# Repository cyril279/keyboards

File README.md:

# One42 | low-profile 42-key Wireless
choc-v2 & v1 switches, MX-spaced, integrated/onboard nrf52840 controller  

# rev41l2 / 41-1353 | low-profile Reviung41 variant
choc-v2 & v1 switches, MX-spaced  

# rev41lp / 41-1350 | low-profile Reviung41 variant
choc-v1 switches, choc-spaced, hotswap, single-color backlit

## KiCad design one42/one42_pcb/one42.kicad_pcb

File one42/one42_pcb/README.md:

[<< Link to Schematic (one42.pdf) >>](./one42.pdf)

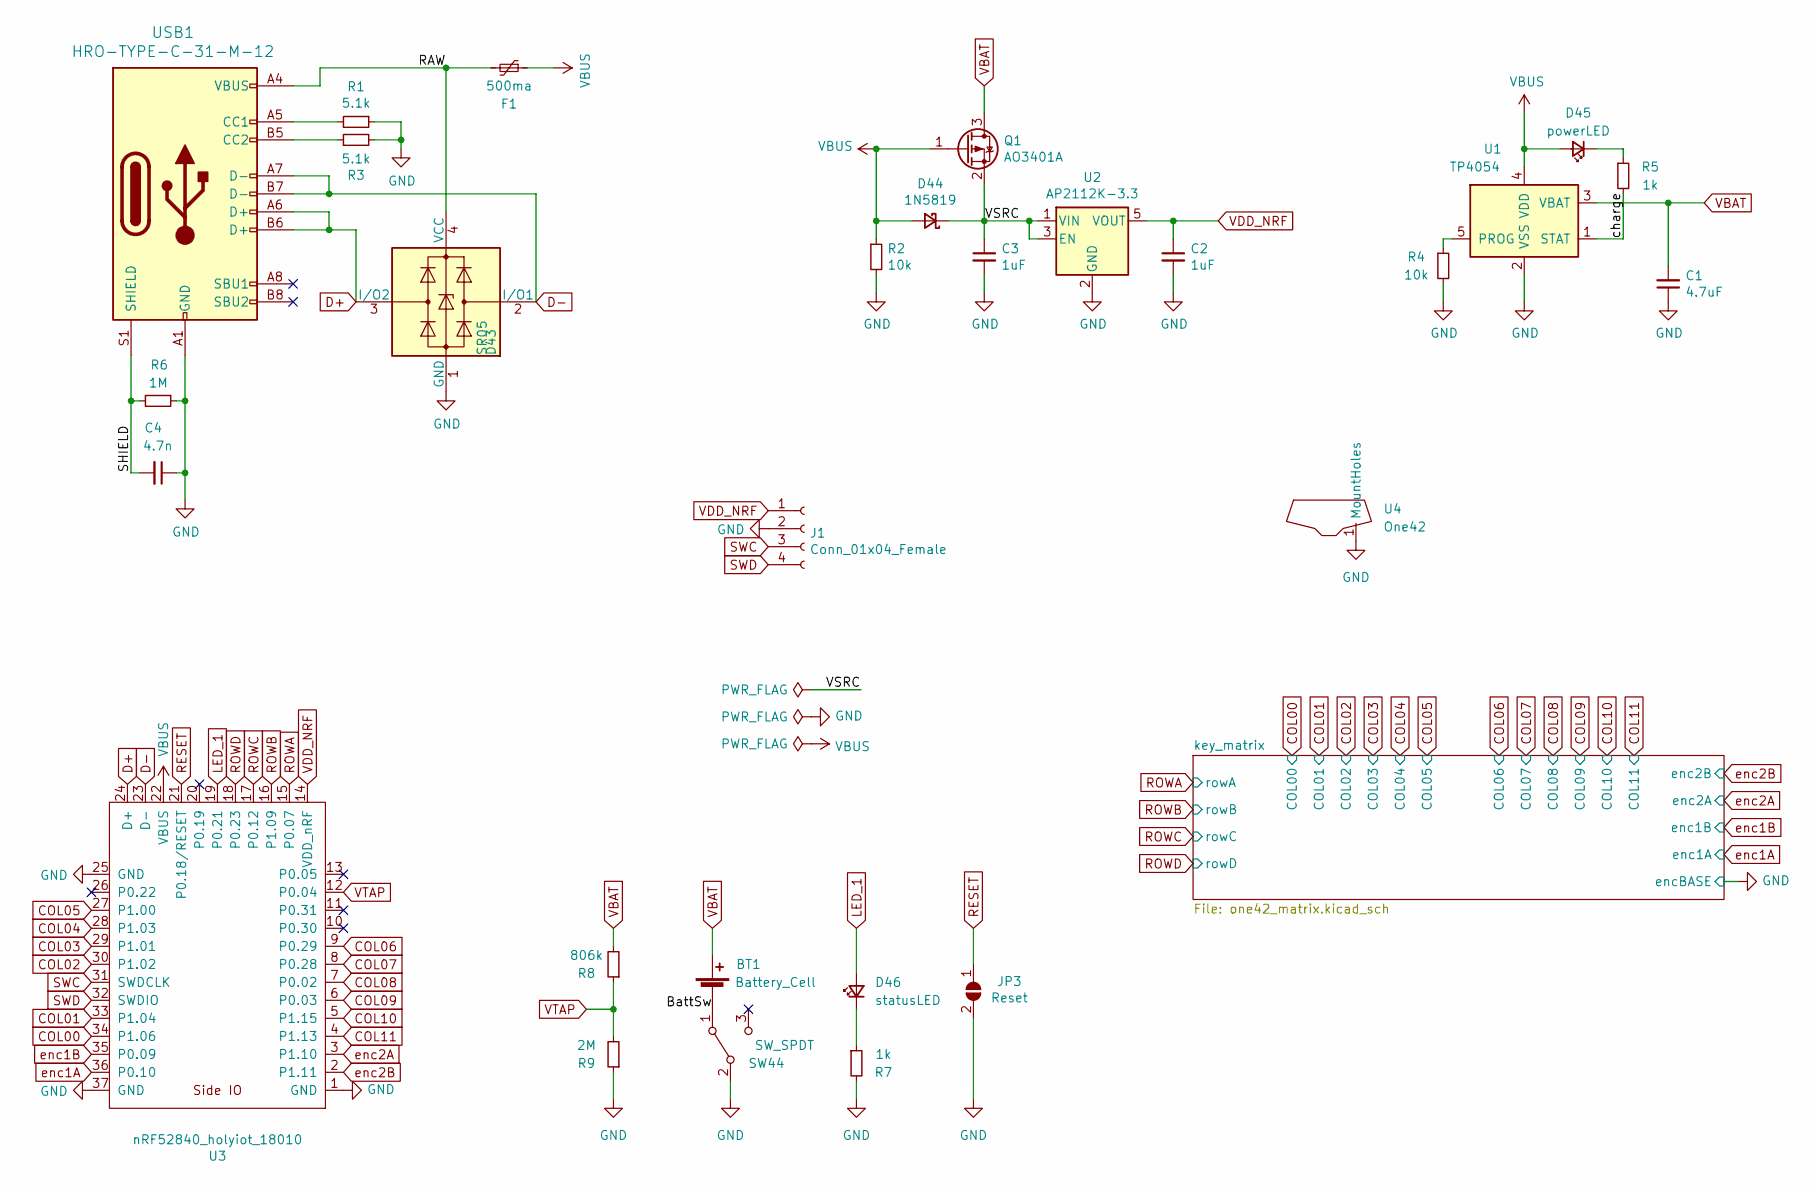
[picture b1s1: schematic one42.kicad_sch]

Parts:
BT1: Battery_Cell; cell_pads
C1: 4.7uF; C_0805_2012Metric; JLC 0805
C2, C3: 1uF; C_0805_2012Metric; JLC 0805
C4: 4.7n; C_1206_3216Metric
D43: SR05; SOT-143
D44: 1N5819; D_SOD-123
D45: powerLED; D_0805_2012Metric
D46: statusLED; D_0805_2012Metric
F1: 500ma; Fuse_1206_3216Metric
J1: Conn_01x04_Female; PinHeader_1x04_P2.54mm_Vertical
JP3: Reset; SolderJumper-2_P1.3mm_Open_RoundedPad1.0x1.5mm
Q1: AO3401A; SOT-23; JLC SOT-23-3L
R1, R3: 5.1k; R_0805_2012Metric; JLC 0805
R2, R4: 10k; R_0805_2012Metric; JLC 0805
R5, R7: 1k; R_0805_2012Metric; JLC 0805
R6: 1M; R_0805_2012Metric; JLC 0805
R8: 806k; R_0805_2012Metric
R9: 2M; R_0805_2012Metric; JLC 0805
SW44: SW_SPDT; switch_SSSS811101
U1: TP4054; SOT-23-5; JLC SOT-23-5
U2: AP2112K-3.3; SOT-23-5
U3: nRF52840_holyiot_18010; nRF52840_holyiot_18010_HS_simple
U4: One42; one42
USB1: HRO-TYPE-C-31-M-12; USB_C_Receptacle_HRO_TYPE-C-31-M-12_handsolder

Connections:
/BattSw: BT1.2 (-), SW44.1 (A)
/RAW: D43.4 (VCC), F1.2, USB1.A4 (VBUS), USB1.A9 (VBUS), USB1.B4 (VBUS), USB1.B9 (VBUS)
/SHIELD: C4.2, R6.2, USB1.S1 (SHIELD)
/VSRC: C3.1, D44.1 (K), Q1.2 (S), U2.1 (VIN), U2.3 (EN)
/charge: R5.2, U1.1 (STAT)
COL00: U3.34 (P1.06); also elsewhere on the board
COL01: U3.33 (P1.04); also elsewhere on the board
COL02: U3.30 (P1.02); also elsewhere on the board
COL03: U3.29 (P1.01); also elsewhere on the board
COL04: U3.28 (P1.03); also elsewhere on the board
COL05: U3.27 (P1.00); also elsewhere on the board
COL06: U3.9 (P0.29); also elsewhere on the board
COL07: U3.8 (P0.28); also elsewhere on the board
COL08: U3.7 (P0.02); also elsewhere on the board
COL09: U3.6 (P0.03); also elsewhere on the board
COL10: U3.5 (P1.15); also elsewhere on the board
COL11: U3.4 (P1.13); also elsewhere on the board
D+: D43.3 (I/O2), U3.24 (D+), USB1.A6 (D+), USB1.B6 (D+)
D-: D43.2 (I/O1), U3.23 (D-), USB1.A7 (D-), USB1.B7 (D-)
GND: C1.1, C2.2, C3.2, C4.1, D43.1 (GND), J1.2, JP3.2 (B), R1.1, R2.2, R3.2, R4.2, R6.1, R7.2, R9.1, SW44.2 (B), U1.2 (VSS), U2.2 (GND), U3.1 (GND), U3.25 (GND), U3.37 (GND), U4.1 (MountHoles), USB1.A1 (GND), USB1.A12 (GND), USB1.B1 (GND), USB1.B12 (GND); also elsewhere on the board
LED_1: D46.2 (A), U3.19 (P0.21)
unnamed: D45.1 (K), R5.1
unnamed: D46.1 (K), R7.1
unnamed: R1.2, USB1.A5 (CC1)
unnamed: R3.1, USB1.B5 (CC2)
unnamed: R4.1, U1.5 (PROG)
RESET: JP3.1 (A), U3.21 (P0.18/RESET)
ROWA: U3.15 (P0.07); also elsewhere on the board
ROWB: U3.16 (P1.09); also elsewhere on the board
ROWC: U3.17 (P0.12); also elsewhere on the board
ROWD: U3.18 (P0.23); also elsewhere on the board
SWC: J1.3, U3.31 (SWDCLK)
SWD: J1.4, U3.32 (SWDIO)
VBAT: BT1.1 (+), C1.2, Q1.3 (D), R8.2, U1.3 (VBAT)
VBUS: D44.2 (A), D45.2 (A), F1.1, Q1.1 (G), R2.1, U1.4 (VDD), U3.22 (VBUS)
VDD_NRF: C2.1, J1.1, U2.5 (VOUT), U3.14 (VDD_nRF)
VTAP: R8.1, R9.2, U3.12 (P0.04)
enc1A: U3.36 (P0.10); also elsewhere on the board
enc1B: U3.35 (P0.09); also elsewhere on the board
enc2A: U3.3 (P1.10); also elsewhere on the board
enc2B: U3.2 (P1.11); also elsewhere on the board

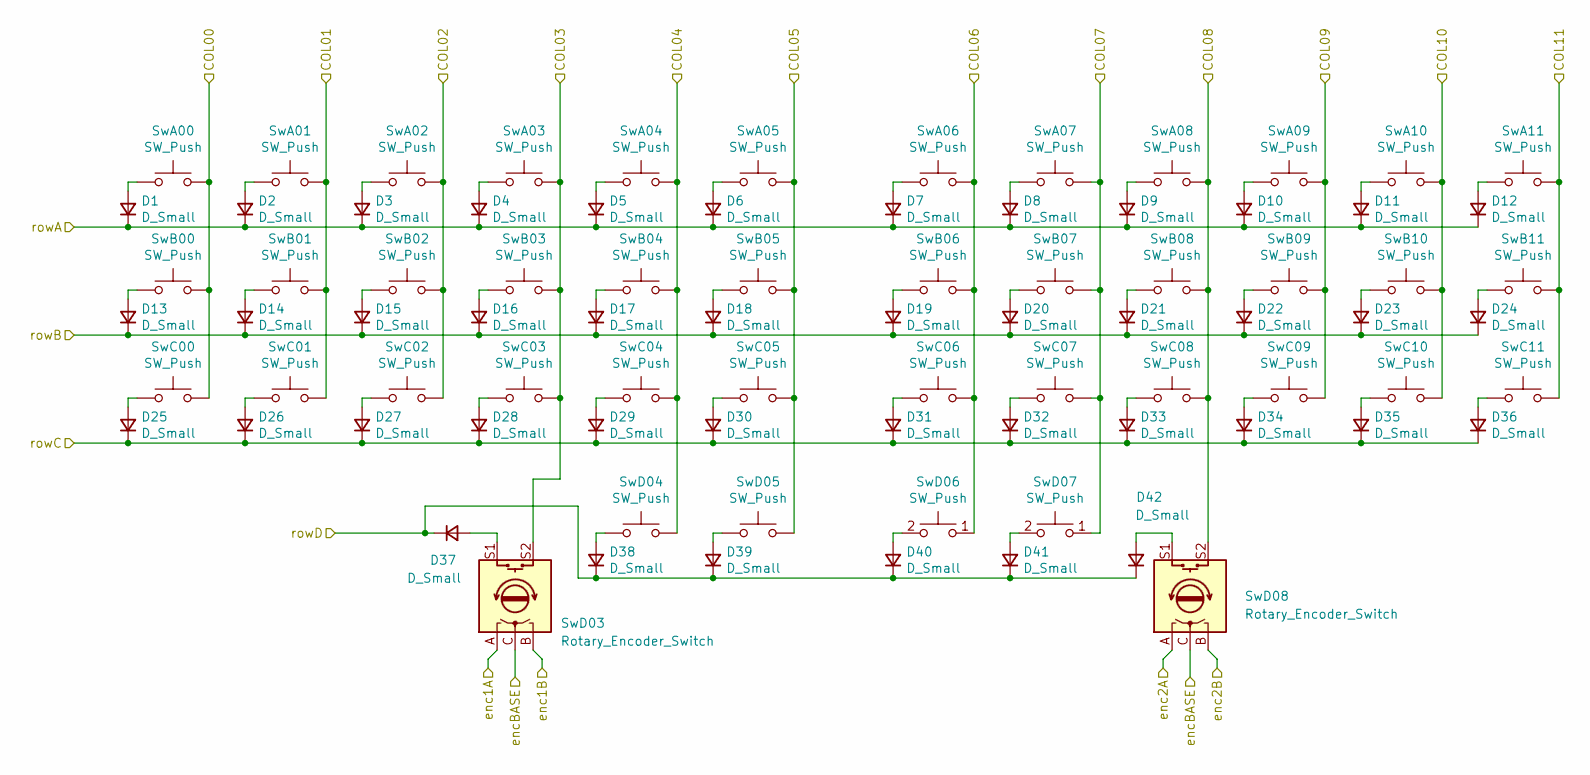
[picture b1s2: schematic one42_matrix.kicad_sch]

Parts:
D1, D2, D3, D4, D5, D6, D7, D8, D9, D10, D11, D12, D13, D14, D15, D16, D17, D18, D19, D20, D21, D22, D23, D24, D25, D26, D27, D28, D29, D30, D31, D32, D33, D34, D35, D36, D37, D38, D39, D40, D41, D42: D_Small; D_SOD-123; JLC SOD-123
SwA00, SwA01, SwA02, SwA03, SwA04, SwA05, SwA06, SwA07, SwA08, SwA09, SwA10, SwA11: SW_Push; pg1353
SwB00, SwB01, SwB02, SwB03, SwB04, SwB05, SwB06, SwB07, SwB08, SwB09, SwB10, SwB11: SW_Push; pg1353
SwC00, SwC01, SwC02, SwC03, SwC04, SwC05, SwC06, SwC07, SwC08, SwC09, SwC10, SwC11: SW_Push; pg1353
SwD03, SwD08: Rotary_Encoder_Switch; pg1353_ec11rotSw
SwD04, SwD05, SwD06, SwD07: SW_Push; pg1353

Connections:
COL00: SwA00.2, SwB00.2, SwC00.2; also elsewhere on the board
COL01: SwA01.2, SwB01.2, SwC01.2; also elsewhere on the board
COL02: SwA02.2, SwB02.2, SwC02.2; also elsewhere on the board
COL03: SwA03.2, SwB03.2, SwC03.2, SwD03.S2; also elsewhere on the board
COL04: SwA04.2, SwB04.2, SwC04.2, SwD04.2; also elsewhere on the board
COL05: SwA05.2, SwB05.2, SwC05.2, SwD05.2; also elsewhere on the board
COL06: SwA06.2, SwB06.2, SwC06.2, SwD06.1; also elsewhere on the board
COL07: SwA07.2, SwB07.2, SwC07.2, SwD07.1; also elsewhere on the board
COL08: SwA08.2, SwB08.2, SwC08.2, SwD08.S2; also elsewhere on the board
COL09: SwA09.2, SwB09.2, SwC09.2; also elsewhere on the board
COL10: SwA10.2, SwB10.2, SwC10.2; also elsewhere on the board
COL11: SwA11.2, SwB11.2, SwC11.2; also elsewhere on the board
GND: SwD03.C, SwD08.C; also elsewhere on the board
unnamed: D1.2 (A), SwA00.1
unnamed: D2.2 (A), SwA01.1
unnamed: D3.2 (A), SwA02.1
unnamed: D4.2 (A), SwA03.1
unnamed: D5.2 (A), SwA04.1
unnamed: D6.2 (A), SwA05.1
unnamed: D7.2 (A), SwA06.1
unnamed: D8.2 (A), SwA07.1
unnamed: D9.2 (A), SwA08.1
unnamed: D10.2 (A), SwA09.1
unnamed: D11.2 (A), SwA10.1
unnamed: D12.2 (A), SwA11.1
unnamed: D13.2 (A), SwB00.1
unnamed: D14.2 (A), SwB01.1
unnamed: D15.2 (A), SwB02.1
unnamed: D16.2 (A), SwB03.1
unnamed: D17.2 (A), SwB04.1
unnamed: D18.2 (A), SwB05.1
unnamed: D19.2 (A), SwB06.1
unnamed: D20.2 (A), SwB07.1
unnamed: D21.2 (A), SwB08.1
unnamed: D22.2 (A), SwB09.1
unnamed: D23.2 (A), SwB10.1
unnamed: D24.2 (A), SwB11.1
unnamed: D25.2 (A), SwC00.1
unnamed: D26.2 (A), SwC01.1
unnamed: D27.2 (A), SwC02.1
unnamed: D28.2 (A), SwC03.1
unnamed: D29.2 (A), SwC04.1
unnamed: D30.2 (A), SwC05.1
unnamed: D31.2 (A), SwC06.1
unnamed: D32.2 (A), SwC07.1
unnamed: D33.2 (A), SwC08.1
unnamed: D34.2 (A), SwC09.1
unnamed: D35.2 (A), SwC10.1
unnamed: D36.2 (A), SwC11.1
unnamed: D37.2 (A), SwD03.S1
unnamed: D38.2 (A), SwD04.1
unnamed: D39.2 (A), SwD05.1
unnamed: D40.2 (A), SwD06.2
unnamed: D41.2 (A), SwD07.2
unnamed: D42.2 (A), SwD08.S1
ROWA: D1.1 (K), D2.1 (K), D3.1 (K), D4.1 (K), D5.1 (K), D6.1 (K), D7.1 (K), D8.1 (K), D9.1 (K), D10.1 (K), D11.1 (K), D12.1 (K); also elsewhere on the board
ROWB: D13.1 (K), D14.1 (K), D15.1 (K), D16.1 (K), D17.1 (K), D18.1 (K), D19.1 (K), D20.1 (K), D21.1 (K), D22.1 (K), D23.1 (K), D24.1 (K); also elsewhere on the board
ROWC: D25.1 (K), D26.1 (K), D27.1 (K), D28.1 (K), D29.1 (K), D30.1 (K), D31.1 (K), D32.1 (K), D33.1 (K), D34.1 (K), D35.1 (K), D36.1 (K); also elsewhere on the board
ROWD: D37.1 (K), D38.1 (K), D39.1 (K), D40.1 (K), D41.1 (K), D42.1 (K); also elsewhere on the board
enc1A: SwD03.A; also elsewhere on the board
enc1B: SwD03.B; also elsewhere on the board
enc2A: SwD08.A; also elsewhere on the board
enc2B: SwD08.B; also elsewhere on the board

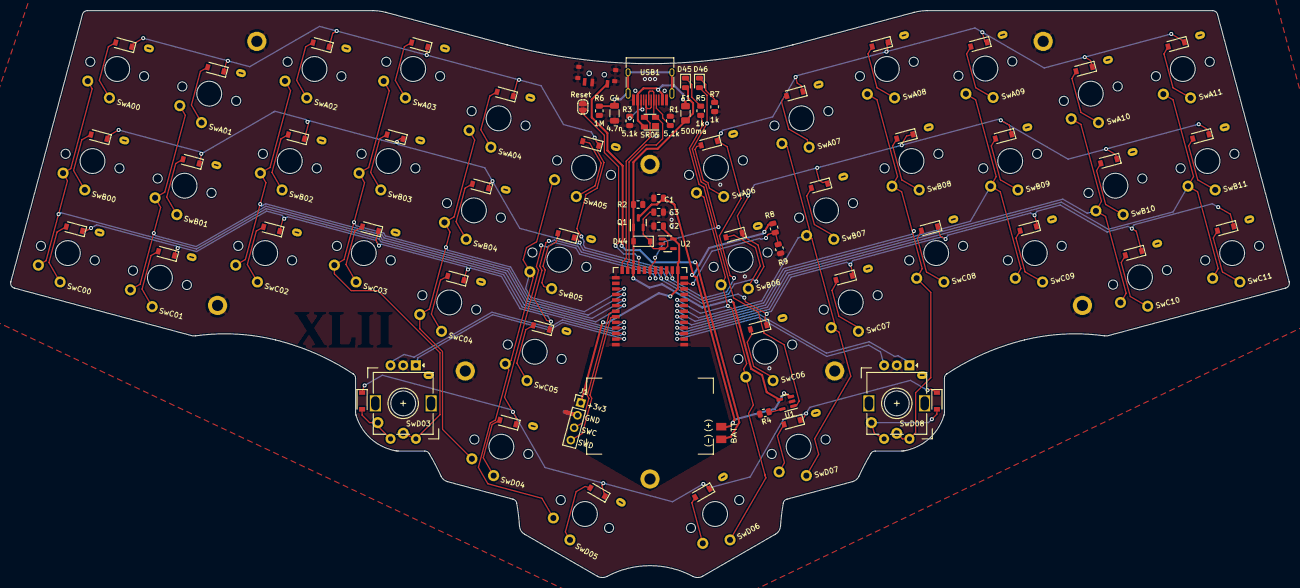
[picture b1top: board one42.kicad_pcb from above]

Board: 2 copper layers, 252.3 x 111.8 mm, 112 parts (0 on the bottom side), 83 nets.

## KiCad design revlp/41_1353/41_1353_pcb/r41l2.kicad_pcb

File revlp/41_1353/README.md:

# Reviung41-lp2
Inspired by the [reviung series](https://github.com/gtips/reviung), designed specifically for Kailh pg1353 (choc-v2) switches.  
(Compatible with choc-v1 switches for those that prefer an mx-spaced reviung41)

This is as low as MX gets.  

**Firmware:** The pinout is the same as the original reviung41, so the existing Reviung41 firmware ([QMK](https://github.com/qmk/qmk_firmware/tree/master/keyboards/reviung41) or [ZMK](https://zmk.dev/docs/hardware#keyboard-shields)) works for this device.  

**[[ Build Guide ]](build.md)** (work-in-progress)  

**[[ Stabilizer Installation ]](build.md#stabilizer-installation)**  
I have not yet provided guidance on how to mod the bar from its stock-state to work with choc-v2 switches.  
The offset/bent portion of the bar needs to be nearly flat.  

# Bill of Materials:  

## Required:  
- 1N4148 Smd diodes, SOD-123 / SOD-80 / miniMelf package (41)  
- Pg1350 switches (41)  
- 2u costar stabilizer
- Pro micro (or equivalent)  

### Bluetooth controller:  
- Battery  
- Batt power switch ([Alps SSSS811101](https://tech.alpsalpine.com/prod/e/html/switch/slide/ssss8/ssss811101.html))

Initial version notes:

Design:
- Diodes can be mounted under switches, or onto back of PCB
- Switchplate can be soldered to PCB or clipped to switches (depending on desired keycap clearance)
- Use of the switchplate prevents opening of switches while soldered

Notes for future iterations:
- pcb: arrows for stabilizer orientation?
- switch cutout dimension (differs per application):
  - 13.95mm square for v2's that are expected to clip into the plate.
  - 13.8mm square for integrated-plate usage, as well as choc v1 usage. <- More likely scenario
- 2u cutout: Make 1mm wider
- PCB-connection points should be through-hole. (eliminate possibility of lifting the pad | stronger connection of pcb-to-switchplate)
- Thickness (differs per application)
  - 1.6mm when v2-switch clip-in (this option has poor cap compatibility, but looks stellar when applicable)
  - 1.2mm when solder-to-PCB (provides maximum cap compatibility. 1.6mm works, but is awfully close)
- Experiment with 18.5mm spacing.

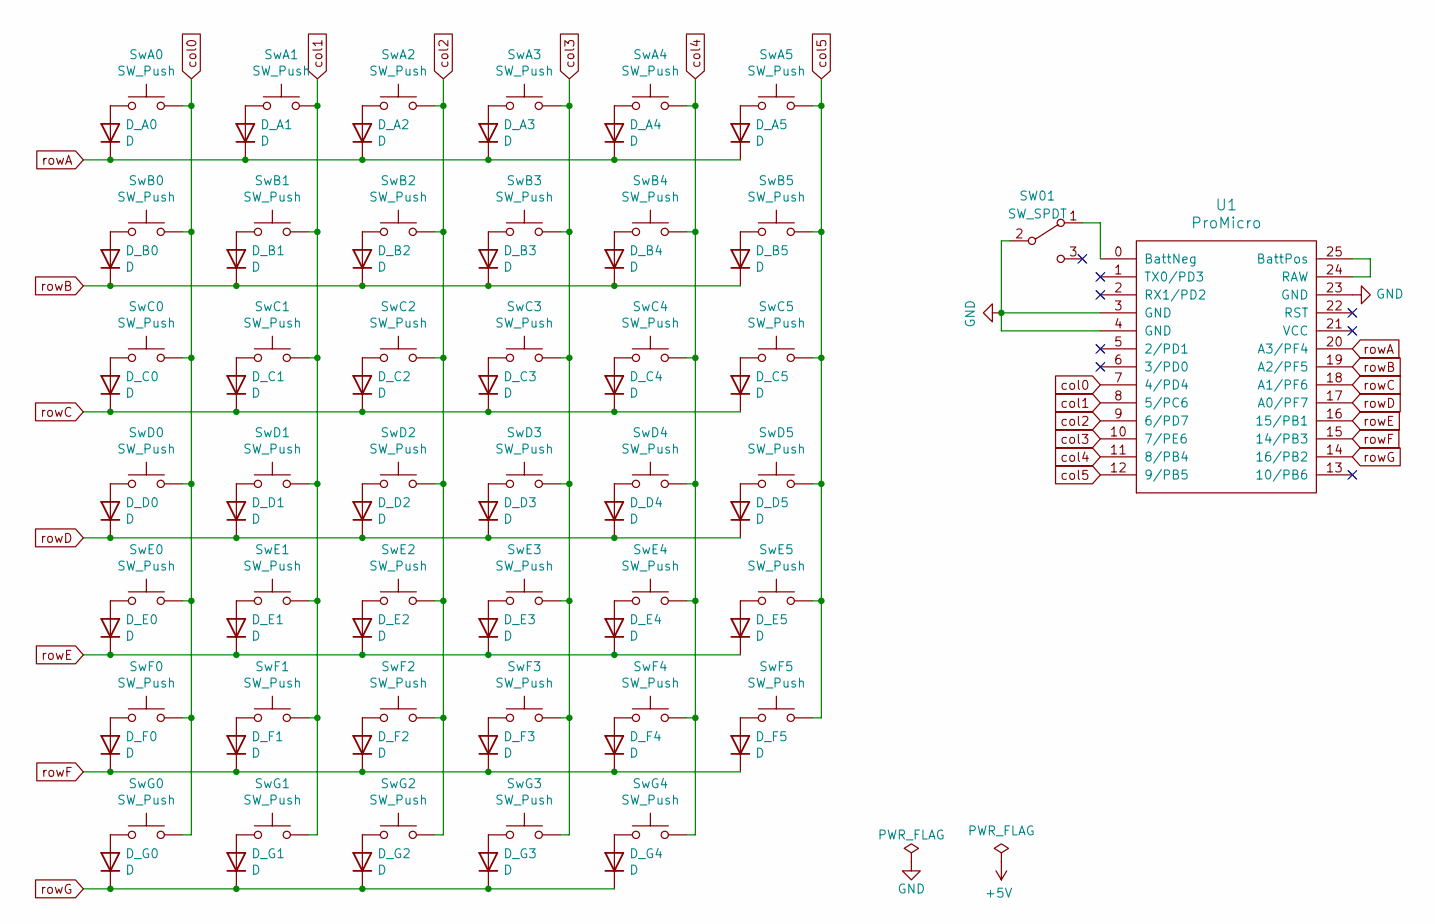
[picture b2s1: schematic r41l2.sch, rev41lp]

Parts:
D_A0, D_A1, D_A2, D_A3, D_A4, D_A5: D; D_MiniMELF_bsides
D_B0, D_B1, D_B2, D_B3, D_B4, D_B5: D; D_MiniMELF_bsides
D_C0, D_C1, D_C2, D_C3, D_C4, D_C5: D; D_MiniMELF_bsides
D_D0, D_D1, D_D2, D_D3, D_D4, D_D5: D; D_MiniMELF_bsides
D_E0, D_E1, D_E2, D_E3, D_E4, D_E5: D; D_MiniMELF_bsides
D_F0, D_F1, D_F2, D_F3, D_F4, D_F5: D; D_MiniMELF_bsides
D_G0, D_G1, D_G2, D_G3, D_G4: D; D_MiniMELF_bsides
SW01: SW_SPDT; switch_SSSS811101
SwA0, SwA1, SwA2, SwA3, SwA4, SwA5: SW_Push; pg1353
SwB0, SwB1, SwB2, SwB3, SwB4, SwB5: SW_Push; pg1353
SwC0, SwC1, SwC2, SwC3, SwC4, SwC5: SW_Push; pg1353
SwD0, SwD1, SwD2, SwD3, SwD4, SwD5: SW_Push; pg1353
SwE0, SwE1, SwE2, SwE3, SwE4, SwE5: SW_Push; pg1353
SwF0, SwF1, SwF2, SwF3, SwF4, SwF5: SW_Push; pg1353
SwG0, SwG1, SwG3, SwG4: SW_Push; pg1353
SwG2: SW_Push; pg1353_reversible_2u
U1: ProMicro; ProMicroNiced

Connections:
GND: SW01.2 (B), U1.3 (GND), U1.4 (GND), U1.23 (GND)
unnamed: D_A0.2 (A), SwA0.1
unnamed: D_A1.2 (A), SwA1.1
unnamed: D_A2.2 (A), SwA2.1
unnamed: D_A3.2 (A), SwA3.1
unnamed: D_A4.2 (A), SwA4.1
unnamed: D_A5.2 (A), SwA5.1
unnamed: D_B0.2 (A), SwB0.1
unnamed: D_B1.2 (A), SwB1.1
unnamed: D_B2.2 (A), SwB2.1
unnamed: D_B3.2 (A), SwB3.1
unnamed: D_B4.2 (A), SwB4.1
unnamed: D_B5.2 (A), SwB5.1
unnamed: D_C0.2 (A), SwC0.1
unnamed: D_C1.2 (A), SwC1.1
unnamed: D_C2.2 (A), SwC2.1
unnamed: D_C3.2 (A), SwC3.1
unnamed: D_C4.2 (A), SwC4.1
unnamed: D_C5.2 (A), SwC5.1
unnamed: D_D0.2 (A), SwD0.1
unnamed: D_D1.2 (A), SwD1.1
unnamed: D_D2.2 (A), SwD2.1
unnamed: D_D3.2 (A), SwD3.1
unnamed: D_D4.2 (A), SwD4.1
unnamed: D_D5.2 (A), SwD5.1
unnamed: D_E0.2 (A), SwE0.1
unnamed: D_E1.2 (A), SwE1.1
unnamed: D_E2.2 (A), SwE2.1
unnamed: D_E3.2 (A), SwE3.1
unnamed: D_E4.2 (A), SwE4.1
unnamed: D_E5.2 (A), SwE5.1
unnamed: D_F0.2 (A), SwF0.1
unnamed: D_F1.2 (A), SwF1.1
unnamed: D_F2.2 (A), SwF2.1
unnamed: D_F3.2 (A), SwF3.1
unnamed: D_F4.2 (A), SwF4.1
unnamed: D_F5.2 (A), SwF5.1
unnamed: D_G0.2 (A), SwG0.1
unnamed: D_G1.2 (A), SwG1.1
unnamed: D_G2.2 (A), SwG2.1
unnamed: D_G3.2 (A), SwG3.1
unnamed: D_G4.2 (A), SwG4.1
unnamed: SW01.1 (A), U1.0 (BattNeg)
unnamed: U1.24 (RAW), U1.25 (BattPos)
col0: SwA0.2, SwB0.2, SwC0.2, SwD0.2, SwE0.2, SwF0.2, SwG0.2, U1.7 (4/PD4)
col1: SwA1.2, SwB1.2, SwC1.2, SwD1.2, SwE1.2, SwF1.2, SwG1.2, U1.8 (5/PC6)
col2: SwA2.2, SwB2.2, SwC2.2, SwD2.2, SwE2.2, SwF2.2, SwG2.2, U1.9 (6/PD7)
col3: SwA3.2, SwB3.2, SwC3.2, SwD3.2, SwE3.2, SwF3.2, SwG3.2, U1.10 (7/PE6)
col4: SwA4.2, SwB4.2, SwC4.2, SwD4.2, SwE4.2, SwF4.2, SwG4.2, U1.11 (8/PB4)
col5: SwA5.2, SwB5.2, SwC5.2, SwD5.2, SwE5.2, SwF5.2, U1.12 (9/PB5)
rowA: D_A0.1 (K), D_A1.1 (K), D_A2.1 (K), D_A3.1 (K), D_A4.1 (K), D_A5.1 (K), U1.20 (A3/PF4)
rowB: D_B0.1 (K), D_B1.1 (K), D_B2.1 (K), D_B3.1 (K), D_B4.1 (K), D_B5.1 (K), U1.19 (A2/PF5)
rowC: D_C0.1 (K), D_C1.1 (K), D_C2.1 (K), D_C3.1 (K), D_C4.1 (K), D_C5.1 (K), U1.18 (A1/PF6)
rowD: D_D0.1 (K), D_D1.1 (K), D_D2.1 (K), D_D3.1 (K), D_D4.1 (K), D_D5.1 (K), U1.17 (A0/PF7)
rowE: D_E0.1 (K), D_E1.1 (K), D_E2.1 (K), D_E3.1 (K), D_E4.1 (K), D_E5.1 (K), U1.16 (15/PB1)
rowF: D_F0.1 (K), D_F1.1 (K), D_F2.1 (K), D_F3.1 (K), D_F4.1 (K), D_F5.1 (K), U1.15 (14/PB3)
rowG: D_G0.1 (K), D_G1.1 (K), D_G2.1 (K), D_G3.1 (K), D_G4.1 (K), U1.14 (16/PB2)

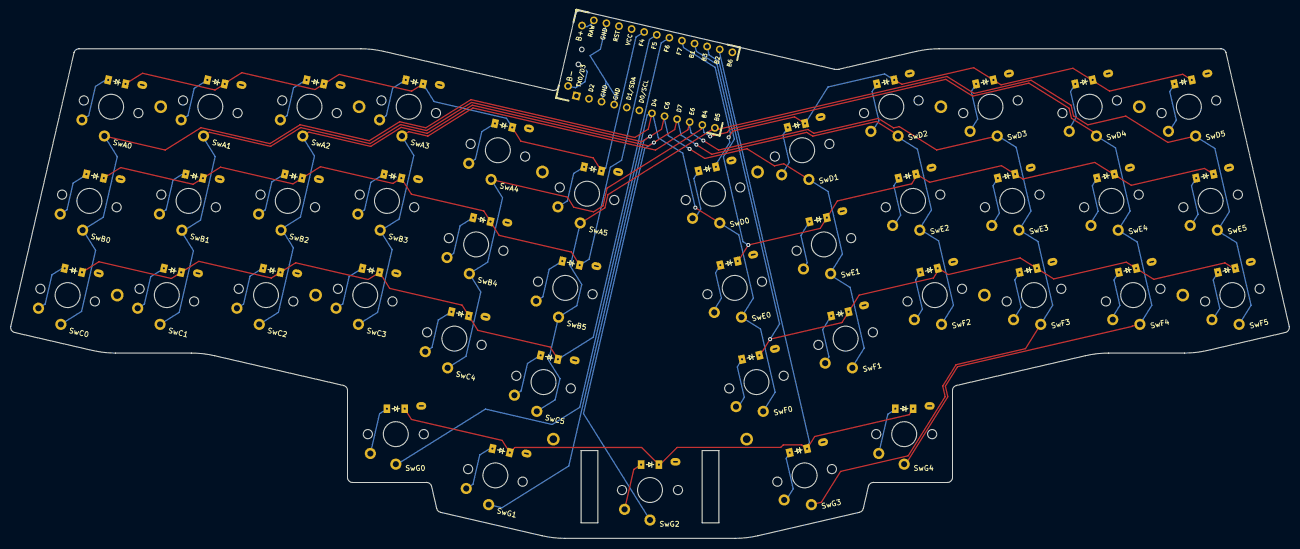
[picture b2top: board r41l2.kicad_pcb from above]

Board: 2 copper layers, 251.3 x 103.7 mm, 84 parts (1 on the bottom side), 57 nets.

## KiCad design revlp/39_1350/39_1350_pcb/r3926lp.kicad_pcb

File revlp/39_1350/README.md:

!! stay tuned for pics and guide !!

# Bill of Materials:  

## Required:  
- 1N4148 Smd diodes, 1206 package (39)  
- Pg1350 kailh sockets (39)  
- Pg1350 switches (39)  
- pro micro (or equivalent)  

## Optional:
- reset switch ([Alps SKSN series](https://tech.alpsalpine.com/prod/e/html/tact/surfacemount/sksn/sksn_list.html))

### Bluetooth controller:  
- battery  
- batt power switch ([Alps SSSS811101](https://tech.alpsalpine.com/prod/e/html/switch/slide/ssss8/ssss811101.html))

### Backlighting:  
- 3528 led's (39)  
- Resistors (see backlighting notes), 1206 package, 1/8 watt (39)  
- 4.7k resistor, 1206 package, 1/8 watt (1)  
- N-channel AO3416 MOSFET, SOT-23 package (1)  

Backlighting notes:  
1. The resistor value needed is determined by specific characteristics of the led's chosen, as well as the voltage supplied by the controller. The specific characteristics can differ for various types and colors of led's.  
2. Use an [led calculator](https://ledcalculator.net/) to determine the resistor value (all ⅛ watt):  
Recommendation: Use minimum resistor needed to protect led, then limit brightness via `BACKLIGHT_LIMIT_VAL` to limit the max to a reasonable value (PWM manged, so more power efficient)  
3. VCC voltage is different for nice!nano from pro-micro; pin 24 is raw on pro-micro, but not on elite-c. **V+ choice matters!**

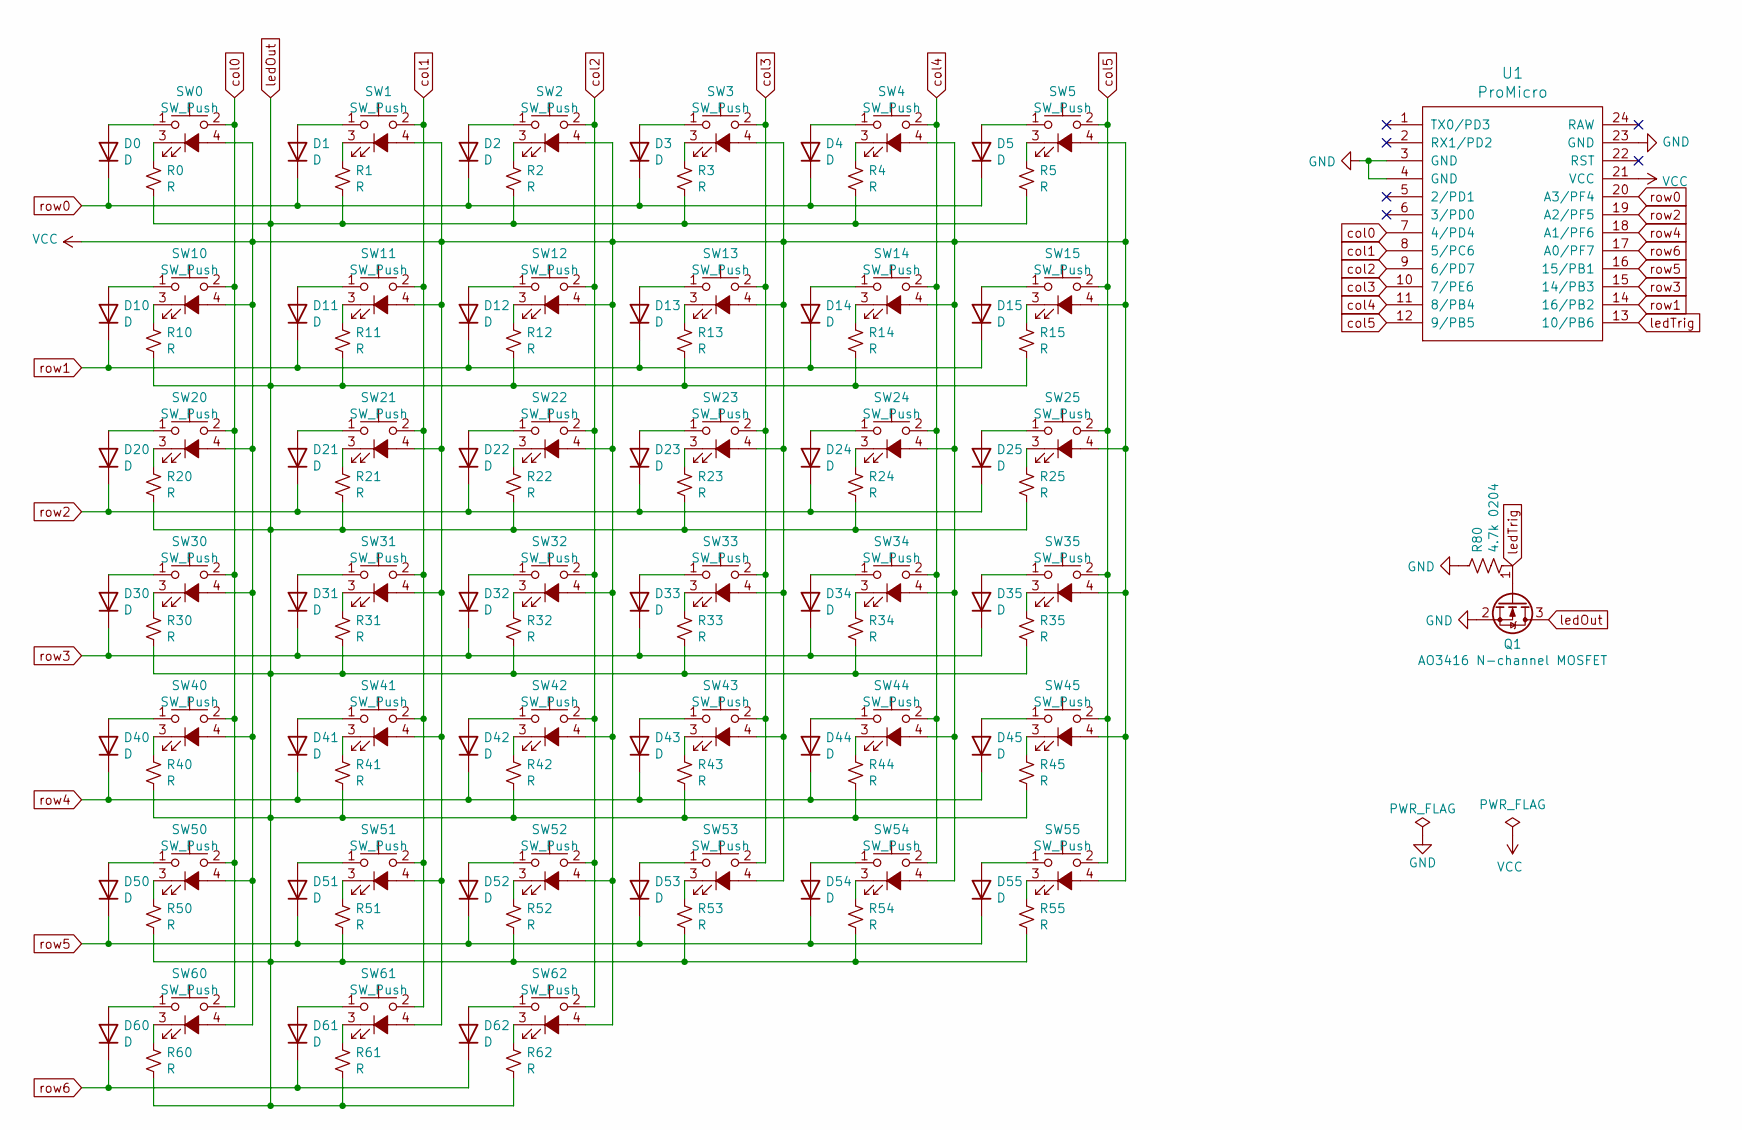
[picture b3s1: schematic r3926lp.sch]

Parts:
D0, D1, D2, D3, D4, D5, D10, D11, D12, D13, D14, D15, D20, D21, D22, D23, D24, D25, D30, D31, D32, D33, D34, D35, D40, D41, D42, D43, D44, D45, D50, D51, D52, D53, D54, D55, D60, D61, D62: D; D_MiniMELF
Q1: AO3416 N-channel MOSFET; SOT-23
R0, R1, R2, R3, R4, R5, R10, R11, R12, R13, R14, R15, R20, R21, R22, R23, R24, R25, R30, R31, R32, R33, R34, R35, R40, R41, R42, R43, R44, R45, R50, R51, R52, R53, R54, R55, R60, R61, R62: R; R_MiniMELF_MMA-0204
R80: 4.7k 0204; R_MiniMELF_MMA-0204
SW0, SW1, SW2, SW3, SW4, SW5, SW10, SW11, SW12, SW13, SW14, SW15, SW20, SW21, SW22, SW23, SW24, SW25, SW30, SW31, SW32, SW33, SW34, SW35, SW40, SW41, SW42, SW43, SW44, SW45, SW50, SW51, SW52, SW53, SW54, SW55, SW60, SW61, SW62: SW_Push; PG1350_socket_smdLed
U1: ProMicro; ArduinoProMicro

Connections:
GND: Q1.2 (S), R80.2, U1.3 (GND), U1.4 (GND), U1.23 (GND)
unnamed: D0.2 (A), SW0.1
unnamed: D1.2 (A), SW1.1
unnamed: D2.2 (A), SW2.1
unnamed: D3.2 (A), SW3.1
unnamed: D4.2 (A), SW4.1
unnamed: D5.2 (A), SW5.1
unnamed: D10.2 (A), SW10.1
unnamed: D11.2 (A), SW11.1
unnamed: D12.2 (A), SW12.1
unnamed: D13.2 (A), SW13.1
unnamed: D14.2 (A), SW14.1
unnamed: D15.2 (A), SW15.1
unnamed: D20.2 (A), SW20.1
unnamed: D21.2 (A), SW21.1
unnamed: D22.2 (A), SW22.1
unnamed: D23.2 (A), SW23.1
unnamed: D24.2 (A), SW24.1
unnamed: D25.2 (A), SW25.1
unnamed: D30.2 (A), SW30.1
unnamed: D31.2 (A), SW31.1
unnamed: D32.2 (A), SW32.1
unnamed: D33.2 (A), SW33.1
unnamed: D34.2 (A), SW34.1
unnamed: D35.2 (A), SW35.1
unnamed: D40.2 (A), SW40.1
unnamed: D41.2 (A), SW41.1
unnamed: D42.2 (A), SW42.1
unnamed: D43.2 (A), SW43.1
unnamed: D44.2 (A), SW44.1
unnamed: D45.2 (A), SW45.1
unnamed: D50.2 (A), SW50.1
unnamed: D51.2 (A), SW51.1
unnamed: D52.2 (A), SW52.1
unnamed: D53.2 (A), SW53.1
unnamed: D54.2 (A), SW54.1
unnamed: D55.2 (A), SW55.1
unnamed: D60.2 (A), SW60.1
unnamed: D61.2 (A), SW61.1
unnamed: D62.2 (A), SW62.1
unnamed: R0.2, SW0.3 (K)
unnamed: R1.2, SW1.3 (K)
unnamed: R2.2, SW2.3 (K)
unnamed: R3.2, SW3.3 (K)
unnamed: R4.2, SW4.3 (K)
unnamed: R5.2, SW5.3 (K)
unnamed: R10.2, SW10.3 (K)
unnamed: R11.2, SW11.3 (K)
unnamed: R12.2, SW12.3 (K)
unnamed: R13.2, SW13.3 (K)
unnamed: R14.2, SW14.3 (K)
unnamed: R15.2, SW15.3 (K)
unnamed: R20.2, SW20.3 (K)
unnamed: R21.2, SW21.3 (K)
unnamed: R22.2, SW22.3 (K)
unnamed: R23.2, SW23.3 (K)
unnamed: R24.2, SW24.3 (K)
unnamed: R25.2, SW25.3 (K)
unnamed: R30.2, SW30.3 (K)
unnamed: R31.2, SW31.3 (K)
unnamed: R32.2, SW32.3 (K)
unnamed: R33.2, SW33.3 (K)
unnamed: R34.2, SW34.3 (K)
unnamed: R35.2, SW35.3 (K)
unnamed: R40.2, SW40.3 (K)
unnamed: R41.2, SW41.3 (K)
unnamed: R42.2, SW42.3 (K)
unnamed: R43.2, SW43.3 (K)
unnamed: R44.2, SW44.3 (K)
unnamed: R45.2, SW45.3 (K)
unnamed: R50.2, SW50.3 (K)
unnamed: R51.2, SW51.3 (K)
unnamed: R52.2, SW52.3 (K)
unnamed: R53.2, SW53.3 (K)
unnamed: R54.2, SW54.3 (K)
unnamed: R55.2, SW55.3 (K)
unnamed: R60.2, SW60.3 (K)
unnamed: R61.2, SW61.3 (K)
unnamed: R62.2, SW62.3 (K)
VCC: SW0.4 (A), SW1.4 (A), SW2.4 (A), SW3.4 (A), SW4.4 (A), SW5.4 (A), SW10.4 (A), SW11.4 (A), SW12.4 (A), SW13.4 (A), SW14.4 (A), SW15.4 (A), SW20.4 (A), SW21.4 (A), SW22.4 (A), SW23.4 (A), SW24.4 (A), SW25.4 (A), SW30.4 (A), SW31.4 (A), SW32.4 (A), SW33.4 (A), SW34.4 (A), SW35.4 (A), SW40.4 (A), SW41.4 (A), SW42.4 (A), SW43.4 (A), SW44.4 (A), SW45.4 (A), SW50.4 (A), SW51.4 (A), SW52.4 (A), SW53.4 (A), SW54.4 (A), SW55.4 (A), SW60.4 (A), SW61.4 (A), SW62.4 (A), U1.21 (VCC)
col0: SW0.2, SW10.2, SW20.2, SW30.2, SW40.2, SW50.2, SW60.2, U1.7 (4/PD4)
col1: SW1.2, SW11.2, SW21.2, SW31.2, SW41.2, SW51.2, SW61.2, U1.8 (5/PC6)
col2: SW2.2, SW12.2, SW22.2, SW32.2, SW42.2, SW52.2, SW62.2, U1.9 (6/PD7)
col3: SW3.2, SW13.2, SW23.2, SW33.2, SW43.2, SW53.2, U1.10 (7/PE6)
col4: SW4.2, SW14.2, SW24.2, SW34.2, SW44.2, SW54.2, U1.11 (8/PB4)
col5: SW5.2, SW15.2, SW25.2, SW35.2, SW45.2, SW55.2, U1.12 (9/PB5)
ledOut: Q1.3 (D), R0.1, R1.1, R2.1, R3.1, R4.1, R5.1, R10.1, R11.1, R12.1, R13.1, R14.1, R15.1, R20.1, R21.1, R22.1, R23.1, R24.1, R25.1, R30.1, R31.1, R32.1, R33.1, R34.1, R35.1, R40.1, R41.1, R42.1, R43.1, R44.1, R45.1, R50.1, R51.1, R52.1, R53.1, R54.1, R55.1, R60.1, R61.1, R62.1
ledTrig: Q1.1 (G), R80.1, U1.13 (10/PB6)
row0: D0.1 (K), D1.1 (K), D2.1 (K), D3.1 (K), D4.1 (K), D5.1 (K), U1.20 (A3/PF4)
row1: D10.1 (K), D11.1 (K), D12.1 (K), D13.1 (K), D14.1 (K), D15.1 (K), U1.14 (16/PB2)
row2: D20.1 (K), D21.1 (K), D22.1 (K), D23.1 (K), D24.1 (K), D25.1 (K), U1.19 (A2/PF5)
row3: D30.1 (K), D31.1 (K), D32.1 (K), D33.1 (K), D34.1 (K), D35.1 (K), U1.15 (14/PB3)
row4: D40.1 (K), D41.1 (K), D42.1 (K), D43.1 (K), D44.1 (K), D45.1 (K), U1.18 (A1/PF6)
row5: D50.1 (K), D51.1 (K), D52.1 (K), D53.1 (K), D54.1 (K), D55.1 (K), U1.16 (15/PB1)
row6: D60.1 (K), D61.1 (K), D62.1 (K), U1.17 (A0/PF7)

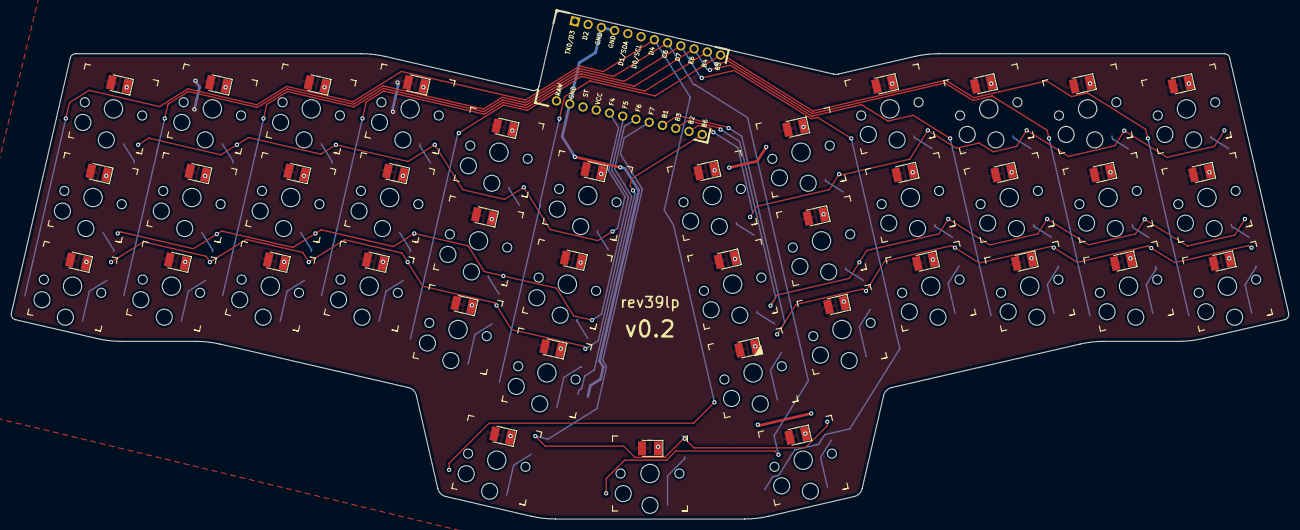
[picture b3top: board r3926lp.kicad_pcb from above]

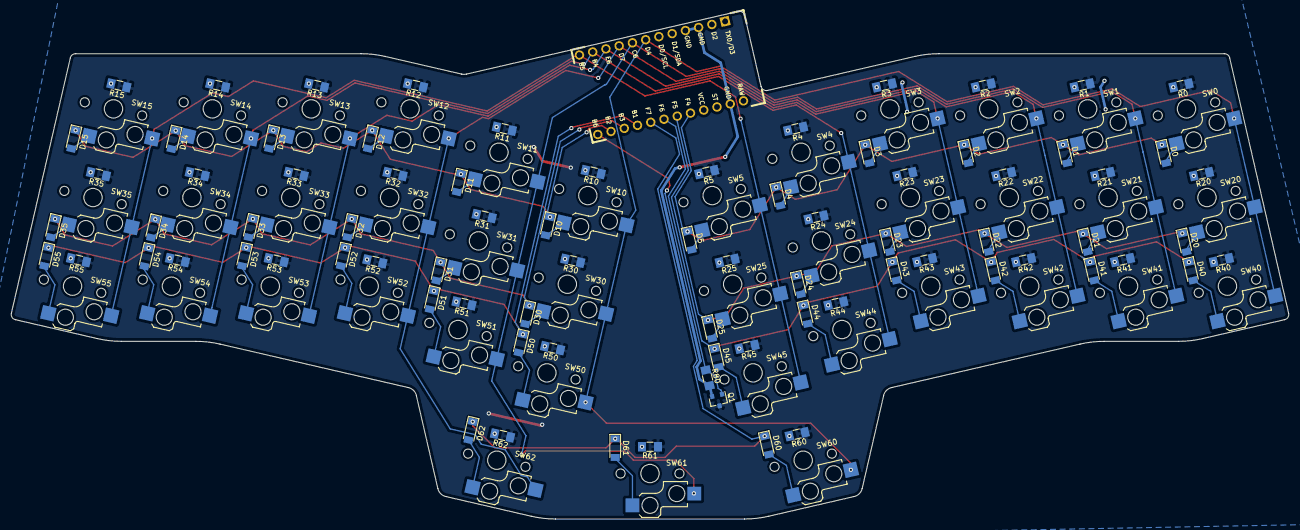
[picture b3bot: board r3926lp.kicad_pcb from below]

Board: 2 copper layers, 238.7 x 94.9 mm, 120 parts (81 on the bottom side), 95 nets.

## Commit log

2021-04-11 Create LICENSE
2021-04-13 Initial B-sides release, r41lp_pcb
2021-04-23 README.md: Update BOM
2021-04-25 Add build photos & update README.md
2021-04-27 README.md: Update zmk & qmk links
2021-04-27 README.md: Update diode information
2021-04-27 Add schematic as pdf
2021-05-01 update README.md: Update QMK link, add build-pic link
2021-05-10 Documentation: Add pg1353 spec
2021-05-10 revlp/build.md: Edited for clarity
2021-05-14 [device] 7teen: 17-position, pg1353
2021-05-17 [keyboard] 7teen: schematic development
2021-05-17 [keyboard] 7teen: schematic & pcb development
2021-05-18 [keyboard] 7teen: pcb development
2021-06-11 [keyboard] 7teen:version update
    Application of lessons-learned
2021-06-14 [kicad] Add single pg1353/1350 footprint
2021-06-14 [keyboard] 7teen: Minor pcb tweaks
2021-06-24 Refactor projects & symbol/footprint libraries
2021-06-25 r41l2: pcb development
2021-06-29 [keyboard] 7teen :: v0.2
2021-06-29 [keyboard] reviung41_1353: Initial release
2021-06-29 [keyboard] reviung39_1350: Initial release
2021-07-09 Adjust README's to match project refactoring
    & initial notes on Reviung41_1353
2021-07-20 [revlp] Update README's
2021-09-08 Remove misplaced directory
2021-09-28 [kicad] Add combo footprint: pg1353_ec11rotSw
2021-09-28 [kicad] Footprint cleanup
2021-10-21 [kicad] Add component: Holyiot-18010
2021-10-21 [kicad] Update combo footprint: pg1353_ec11rotSw
2021-10-21 [kicad] Update pg1353.kicad_mod
2021-10-21 [kicad] Add fuse_1206.step to 3d library
2021-10-22 [keyboard] Introduce one42
    Long Live Ahokore!
2021-10-22 41_1350 Readme: Update ZMK-config url
2021-11-09 [project] One42: Update schematic & PDF
2021-11-09 [project] one42: Add README.md
2021-11-16 [kicad] migrate libraries to 5.99x
2021-11-16 One42: Promote to own directory
2021-11-18 [kicad] .gitignore additions
    * 'fp-info-cache' is regenerated each time Kicad is used, so does not need to be carried through the repo.
    * Ignore 'backup' directories throughout this repo
2021-11-18 README.md: Update 'Thank You'
2021-11-18 [kicad] Move '3d-files' into relevant component library
2021-11-19 one42/README.md: Add lessons-learned
2021-11-21 [one42] Add project photos
2021-11-21 one42/README.md: Wording
2021-11-23 [one42] Add skidPlate
2021-11-23 [one42] Add cover
2021-11-23 [one42] Add switchPlate
2021-11-23 [one42] relocate kicad-project-footprint lib
2021-11-29 [one42] Fabrication files: pcb v0.1
2021-11-29 [one42] README.md: Update 'Thank You'
2021-12-01 keeblib.pretty: Reduce size of battery-cell_pads
2021-12-01 [one42] version 1.0
    - Relocated corner-thumb switch diodes
    - Removed encoder base-supply option
    - Fixed 'R5' silkscreen
    - Fixed programmer-header V+ to 3v3
    - Moved power sw. inboard
    - Mounting holes routed to ground
2021-12-01 [one42] Version 1.0: Component-layout tweaks
    - Moved power sw. to left-side of USB
    - Moved LED's both to right-side of USB
2021-12-01 [one42] Version 1.0: Cleanup
2021-12-01 [kicad] Update keeblib/keebMCU 3d-model associations
2021-12-01 [one42] Add fabrication files
2021-12-01 [one42] Add README
2021-12-08 [one42] Added photos & updated README.md
2021-12-09 [one42] Remove non-archived gerber files
2021-12-17 [one42] Update README & add photos
2021-12-18 Add project README.md, & additional project photos
2022-07-01 Readme.md: Firmware link redirected to upstream QMK
